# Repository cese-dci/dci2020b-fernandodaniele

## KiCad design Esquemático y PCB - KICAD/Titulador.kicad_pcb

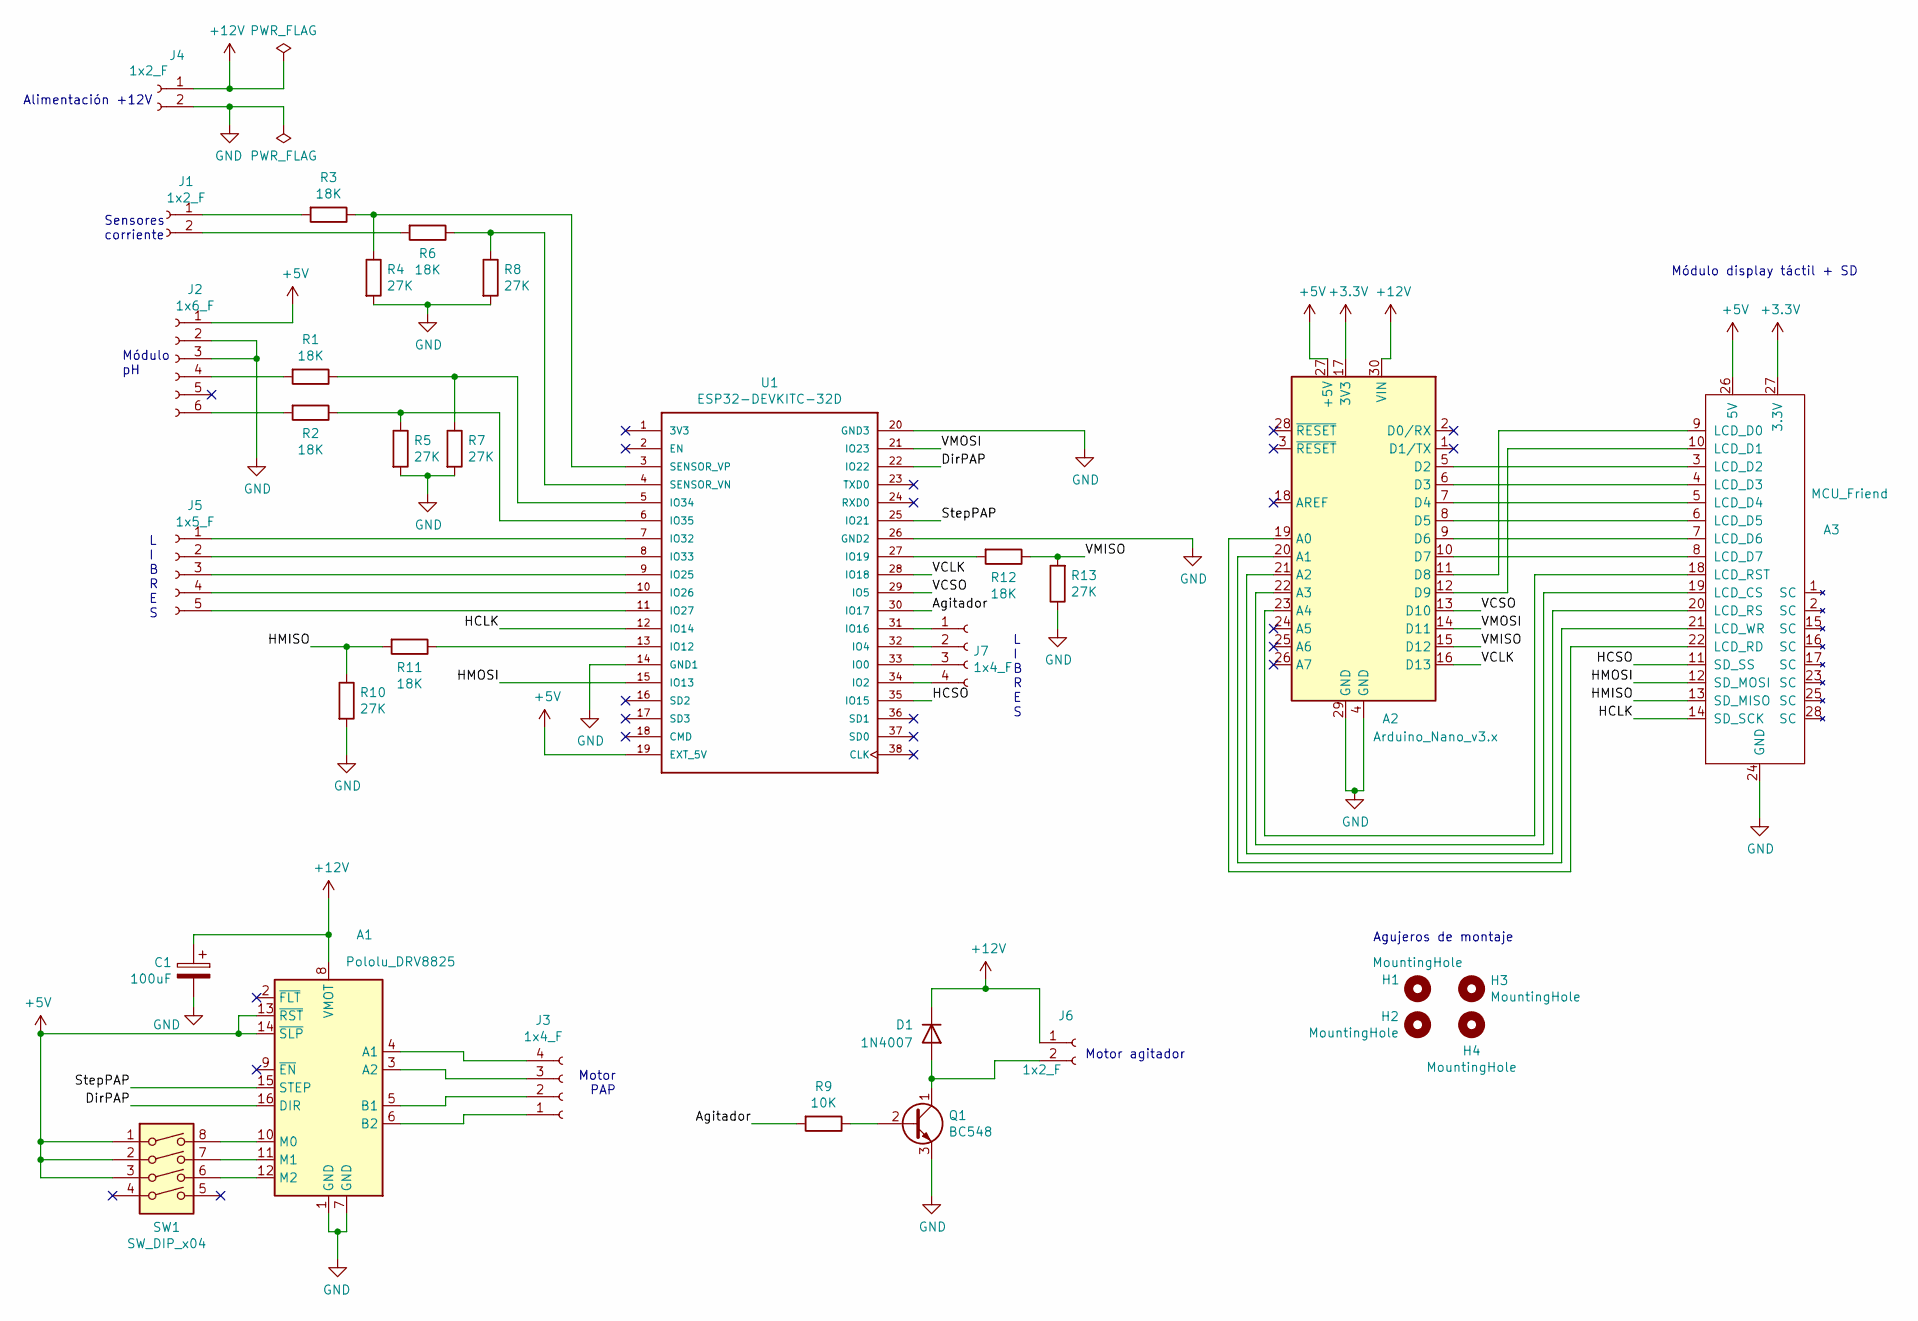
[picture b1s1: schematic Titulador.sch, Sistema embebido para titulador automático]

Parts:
A1: Pololu_DRV8825; Pololu_Breakout-16_15.2x20.3mm
A2: Arduino_Nano_v3.x; Arduino_Nano
A3: MCU_Friend; MCUFriend
C1: 100uF; CP_Radial_D7.5mm_P2.50mm
D1: 1N4007; D_A-405_P7.62mm_Horizontal
H1, H2, H3, H4: MountingHole; MountingHole_3mm
J1, J4, J6: 1x2_F; PinSocket_1x02_P2.54mm_Vertical
J2: 1x6_F; PinSocket_1x06_P2.54mm_Vertical
J3, J7: 1x4_F; PinSocket_1x04_P2.54mm_Vertical
J5: 1x5_F; PinSocket_1x05_P2.54mm_Vertical
Q1: BC548; TO-92L_Wide
R1, R2, R3, R6, R11, R12: 18K; R_Axial_DIN0207_L6.3mm_D2.5mm_P7.62mm_Horizontal
R4, R5, R7, R8, R10, R13: 27K; R_Axial_DIN0207_L6.3mm_D2.5mm_P7.62mm_Horizontal
R9: 10K; R_Axial_DIN0207_L6.3mm_D2.5mm_P7.62mm_Horizontal
SW1: SW_DIP_x04; SW_DIP_SPSTx04_Slide_6.7x11.72mm_W7.62mm_P2.54mm_LowProfile
U1: ESP32-DEVKITC-32D; MODULE_ESP32-DEVKITC-32D

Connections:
+3V3: A2.17 (3V3), A3.27 (3.3V)
+5V: A1.13 (~RST), A1.14 (~SLP), A2.27 (+5V), A3.26 (5V), J2.1, SW1.1, SW1.2, SW1.3, U1.19 (EXT_5V)
+12V: A1.8 (VMOT), A2.30 (VIN), C1.1, D1.1 (K), J4.1, J6.1
/Agitador: R9.2, U1.30 (IO17)
/DirPAP: A1.16 (DIR), U1.22 (IO22)
/HCLK: A3.14 (SD_SCK), U1.12 (IO14)
/HCSO: A3.11 (SD_SS), U1.35 (IO15)
/HMISO: A3.13 (SD_MISO), R10.1, R11.2
/HMOSI: A3.12 (SD_MOSI), U1.15 (IO13)
/StepPAP: A1.15 (STEP), U1.25 (IO21)
/VCLK: A2.16 (D13), U1.28 (IO18)
/VCSO: A2.13 (D10), U1.29 (IO5)
/VMISO: A2.15 (D12), R12.1, R13.2
/VMOSI: A2.14 (D11), U1.21 (IO23)
GND: A1.1 (GND), A1.7 (GND), A2.4 (GND), A2.29 (GND), A3.24 (GND), C1.2, J2.2, J2.3, J4.2, Q1.3 (E), R4.2, R5.2, R7.2, R8.2, R10.2, R13.1, U1.14 (GND1), U1.20 (GND3), U1.26 (GND2)
unnamed: A1.3 (A2), J3.3
unnamed: A1.4 (A1), J3.4
unnamed: A1.5 (B1), J3.2
unnamed: A1.6 (B2), J3.1
unnamed: A1.10 (M0), SW1.8
unnamed: A1.11 (M1), SW1.7
unnamed: A1.12 (M2), SW1.6
unnamed: A2.5 (D2), A3.3 (LCD_D2)
unnamed: A2.6 (D3), A3.4 (LCD_D3)
unnamed: A2.7 (D4), A3.5 (LCD_D4)
unnamed: A2.8 (D5), A3.6 (LCD_D5)
unnamed: A2.9 (D6), A3.7 (LCD_D6)
unnamed: A2.10 (D7), A3.8 (LCD_D7)
unnamed: A2.11 (D8), A3.9 (LCD_D0)
unnamed: A2.12 (D9), A3.10 (LCD_D1)
unnamed: A2.19 (A0), A3.22 (LCD_RD)
unnamed: A2.20 (A1), A3.21 (LCD_WR)
unnamed: A2.21 (A2), A3.20 (LCD_RS)
unnamed: A2.22 (A3), A3.19 (LCD_CS)
unnamed: A2.23 (A4), A3.18 (LCD_RST)
unnamed: D1.2 (A), J6.2, Q1.1 (C)
unnamed: J1.1, R3.2
unnamed: J1.2, R6.2
unnamed: J2.4, R1.2
unnamed: J2.6, R2.2
unnamed: J5.1, U1.7 (IO32)
unnamed: J5.2, U1.8 (IO33)
unnamed: J5.3, U1.9 (IO25)
unnamed: J5.4, U1.10 (IO26)
unnamed: J5.5, U1.11 (IO27)
unnamed: J7.1, U1.31 (IO16)
unnamed: J7.2, U1.32 (IO4)
unnamed: J7.3, U1.33 (IO0)
unnamed: J7.4, U1.34 (IO2)
unnamed: Q1.2 (B), R9.1
unnamed: R1.1, R7.1, U1.5 (IO34)
unnamed: R2.1, R5.1, U1.6 (IO35)
unnamed: R3.1, R4.1, U1.3 (SENSOR_VP)
unnamed: R6.1, R8.1, U1.4 (SENSOR_VN)
unnamed: R11.1, U1.13 (IO12)
unnamed: R12.2, U1.27 (IO19)

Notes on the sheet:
Alimentación +12V
Módulo pH
Motor PAP
L I B R E S
Motor agitador
Módulo display táctil + SD
Sensores corriente
Agujeros de montaje

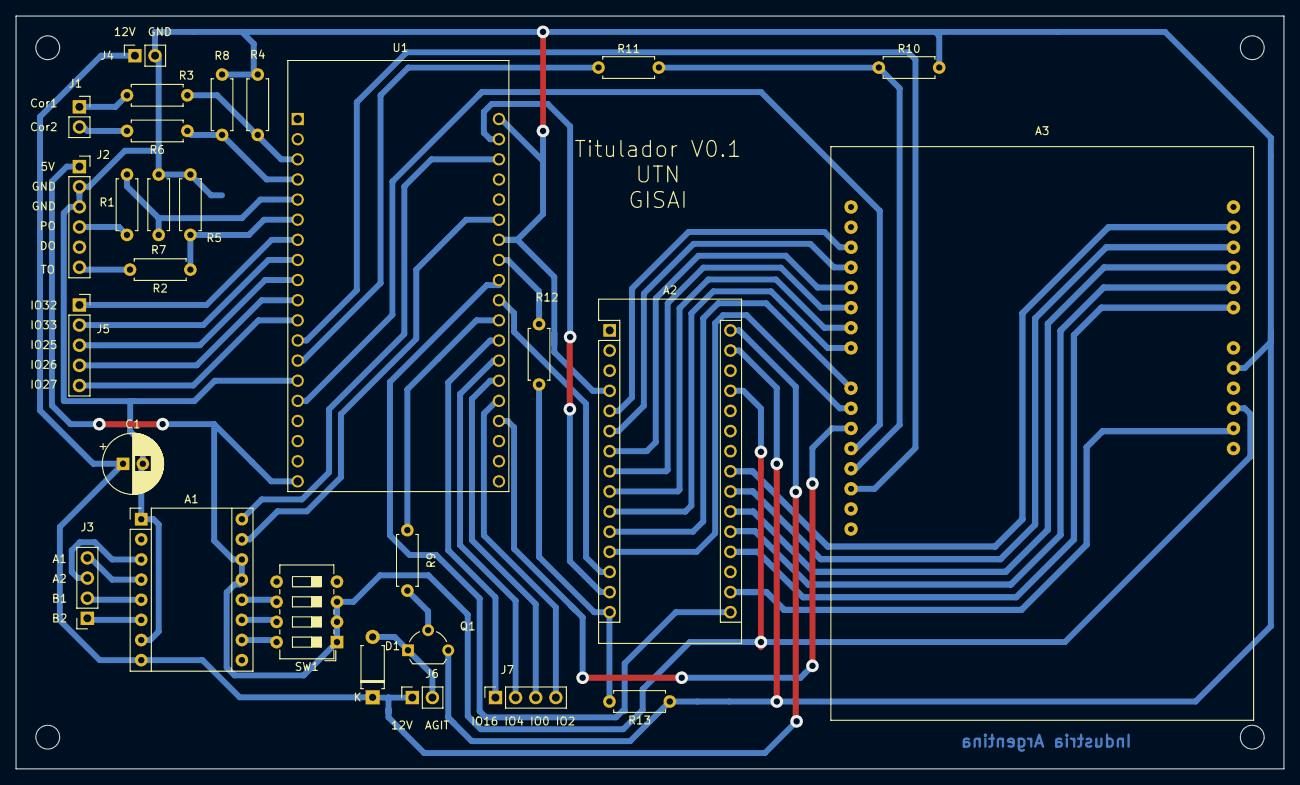
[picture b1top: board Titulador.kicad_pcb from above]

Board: 2 copper layers, 160.0 x 95.0 mm, 32 parts (0 on the bottom side), 56 nets.

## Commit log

2020-10-09 Entrega esquematico
2020-10-23 Se agrega PCB
2020-10-29 Se crean carpetas, se actualiza pcb y esquema
2020-10-30 Se finaliza pcb y corrige segun primera revision
2020-10-30 Se eliminan archivos
2020-11-04 Correcciones revision pcb
